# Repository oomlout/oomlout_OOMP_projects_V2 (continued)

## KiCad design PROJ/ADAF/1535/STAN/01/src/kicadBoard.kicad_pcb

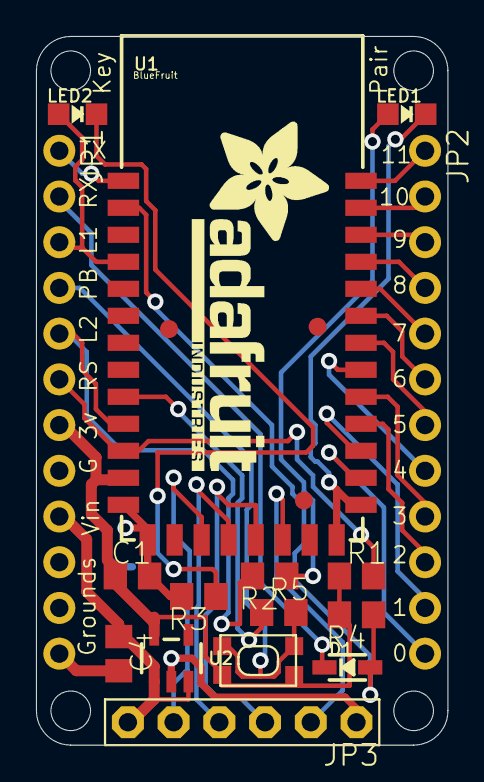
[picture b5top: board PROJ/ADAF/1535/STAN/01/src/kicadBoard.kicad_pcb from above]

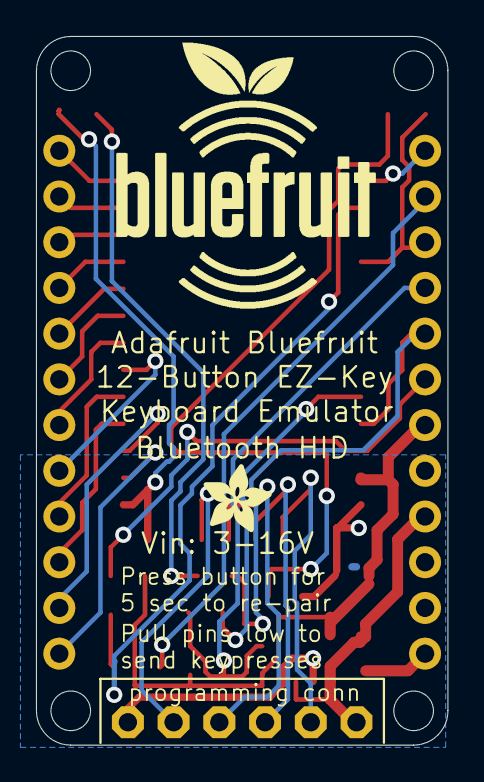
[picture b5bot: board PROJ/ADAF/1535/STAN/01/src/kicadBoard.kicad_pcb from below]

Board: 2 copper layers, 22.9 x 39.4 mm, 26 parts (2 on the bottom side), 29 nets.

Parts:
@HOLE0, @HOLE1, @HOLE2, @HOLE3: (no value)
C1, C4: 10uF; C0805
D1: 1N4148; SOD-323
FID1, FID2, FID3: FIDUCIAL""; FIDUCIAL_1MM
JP1, JP2: 1X12-CB
JP3: 1X06-BIG
LED1: RED; CHIPLED_0805_NOOUTLINE
LED2: GREEN; CHIPLED_0805_NOOUTLINE
R1, R4: 10K; R0805
R2, R3: 1K; R0805
R5: 2.2K; R0805
SW1: SPST_TACT-KMR2; KMR2
U1: BlueFruit; BLUETOOTH_MODULE
U2: MIC5225; SOT23-5
U$2: BLUEFRUITLOGO_150MM
U$3: ADAFRUIT_3.5MM
U$4: ADAFRUIT_TEXT_20MM

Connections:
+3V3: C1.1, JP1.7, R1.1, R4.2, SW1.1, SW1.3, U1.12, U2.5
+5V: C4.1, JP1.9, JP3.6, U2.1, U2.3
ACT_LED: JP1.5, R2.2, U1.10
CLK: JP3.2, U1.19
CS: JP3.5, U1.16
GND: C1.2, C4.2, JP1.8, JP1.10, JP1.11, JP1.12, JP3.1, LED1.C, R3.2, U1.13, U1.14, U1.21, U1.22, U2.2
MISO: JP3.3, U1.18
MOSI: JP3.4, U1.17
unnamed: JP2.5, U1.30
unnamed: LED1.A, R2.1
unnamed: LED2.C, R3.1
unnamed: JP2.12, U1.23
unnamed: JP2.11, U1.24
unnamed: JP2.10, U1.25
unnamed: JP2.9, U1.26
unnamed: JP2.8, U1.27
unnamed: JP2.7, U1.28
unnamed: JP2.6, U1.29
unnamed: JP2.4, U1.31
unnamed: JP2.3, U1.32
unnamed: JP2.2, U1.33
unnamed: JP2.1, U1.34
PAIR_2: JP1.4, R5.2, SW1.2, SW1.4
PAIR_BTN: R5.1, U1.9
RESET: JP1.6, R1.2, U1.11
RTS: JP1.3, LED2.A, U1.4
RXD: D1.A, R4.1, U1.2
RXD_5V: D1.C, JP1.2
TXD: JP1.1, U1.1

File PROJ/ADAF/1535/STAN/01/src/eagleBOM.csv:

"Part";"Value";"Device";"Package";"Description";"BOM";
"C1";"10uF";"C-USC0805";"C0805";"CAPACITOR, American symbol";"";
"C4";"10uF";"C-USC0805";"C0805";"CAPACITOR, American symbol";"";
"D1";"1N4148";"DIODESOD-323";"SOD-323";"Diode";"";
"FID1";"FIDUCIAL""";"FIDUCIAL""";"FIDUCIAL_1MM";"Fiducial Alignment Points";"EXCLUDE";
"FID2";"FIDUCIAL""";"FIDUCIAL""";"FIDUCIAL_1MM";"Fiducial Alignment Points";"EXCLUDE";
"FID3";"FIDUCIAL""";"FIDUCIAL""";"FIDUCIAL_1MM";"Fiducial Alignment Points";"EXCLUDE";
"JP1";"";"PINHD-1X12-CB";"1X12-CB";"PIN HEADER";"";
"JP2";"";"PINHD-1X12-CB";"1X12-CB";"PIN HEADER";"";
"JP3";"";"PINHD-1X6B";"1X06-BIG";"PIN HEADER";"";
"LED1";"RED";"LED0805_NOOUTLINE";"CHIPLED_0805_NOOUTLINE";"LED";"";
"LED2";"GREEN";"LED0805_NOOUTLINE";"CHIPLED_0805_NOOUTLINE";"LED";"";
"R1";"10K";"R-US_R0805";"R0805";"RESISTOR, American symbol";"";
"R2";"1K";"R-US_R0805";"R0805";"RESISTOR, American symbol";"";
"R3";"1K";"R-US_R0805";"R0805";"RESISTOR, American symbol";"";
"R4";"10K";"R-US_R0805";"R0805";"RESISTOR, American symbol";"";
"R5";"2.2K";"R-US_R0805";"R0805";"RESISTOR, American symbol";"";
"SW1";"SPST_TACT-KMR2";"SPST_TACT-KMR2";"KMR2";"SMT 6mm switch, EVQQ2 series";"";
"U1";"BlueFruit";"BLUETOOTH_MODULE";"BLUETOOTH_MODULE";"BLUETOOTH MODULE";"";
"U2";"MIC5225";"VREG_SOT23-5";"SOT23-5";"SOT23-5 Fixed Voltage Regulators";"";

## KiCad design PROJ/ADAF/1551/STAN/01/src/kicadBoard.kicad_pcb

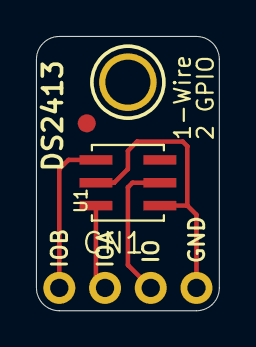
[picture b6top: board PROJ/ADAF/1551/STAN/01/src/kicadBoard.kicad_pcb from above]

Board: 2 copper layers, 10.2 x 15.2 mm, 5 parts (1 on the bottom side), 4 nets.

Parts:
CN1: 1X4-CLEANBIG; 1X04-CLEANBIG
FID1: FIDUCIAL""; FIDUCIAL_1MM
U1: DS2413; DS2413_TSOC6L
U$3: ADAFRUIT_3.5MM
U$4: MOUNTINGHOLE2.5; MOUNTINGHOLE_2.5_PLATED

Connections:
GND: CN1.4, U1.1, U1.5
IO: CN1.3, U1.2
PIOA: CN1.2, U1.6
PIOB: CN1.1, U1.4

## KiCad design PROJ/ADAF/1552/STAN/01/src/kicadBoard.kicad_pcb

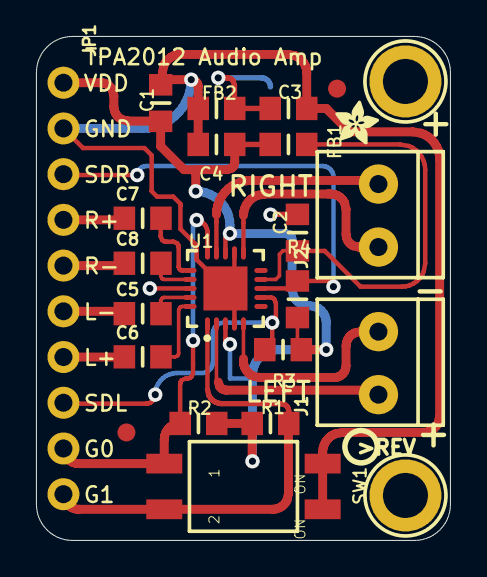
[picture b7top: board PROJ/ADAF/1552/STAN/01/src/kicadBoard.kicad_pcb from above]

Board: 2 copper layers, 23.0 x 28.0 mm, 25 parts (0 on the bottom side), 20 nets.

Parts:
C1: 10µF; _0805MP
C2, C3, C4: 0.1µF; _0805MP
C5, C6, C7, C8: 1µF; _0805MP
FB1, FB2: ferrite; _0805MP
FID1, FID2: FIDUCIAL""; FIDUCIAL_1MM
J1, J2: TERMBLOCK_1X2-3.5MM
JP1: 1X10_ROUND70
R1, R2, R3, R4: 100K; _0805MP
SW1: DIPSWITCH_2PIN
U1: TS2012; WQFN20
U$20, U$21: MOUNTINGHOLE2.5_THICK; MOUNTINGHOLE_2.5_PLATED_THICK
U$22: ADAFRUIT_2.5MM
U$23: PCBFEAT-REV-040

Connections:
AGND: C2.2, C3.2, FB2.2, U1.18
AVDD: C2.1, FB1.2, U1.9
GAIN0: JP1.9, R2.1, SW1.1OFF, U1.15
GAIN1: JP1.10, R1.1, SW1.2OFF, U1.1
GND: C1.2, C3.1, C4.2, FB2.1, JP1.2, SW1.1ON, SW1.2ON, U1.4, U1.12, U1.21
IN_L_N: C5.1, JP1.6
IN_L_P: C6.1, JP1.7
IN_R_N: C8.1, JP1.5
IN_R_P: C7.1, JP1.4
unnamed: C6.2, U1.20
unnamed: C5.2, U1.19
unnamed: C8.2, U1.17
unnamed: C7.2, U1.16
OUT_L_N: J1.1, U1.5
OUT_L_P: J1.2, U1.2
OUT_R_N: J2.2, U1.11
OUT_R_P: J2.1, U1.14
SHUTDOWN_L: JP1.8, R3.1, U1.7
SHUTDOWN_R: JP1.3, R4.1, U1.8
VDD: C1.1, C4.1, FB1.1, JP1.1, R1.2, R2.2, R3.2, R4.2, U1.3, U1.13
